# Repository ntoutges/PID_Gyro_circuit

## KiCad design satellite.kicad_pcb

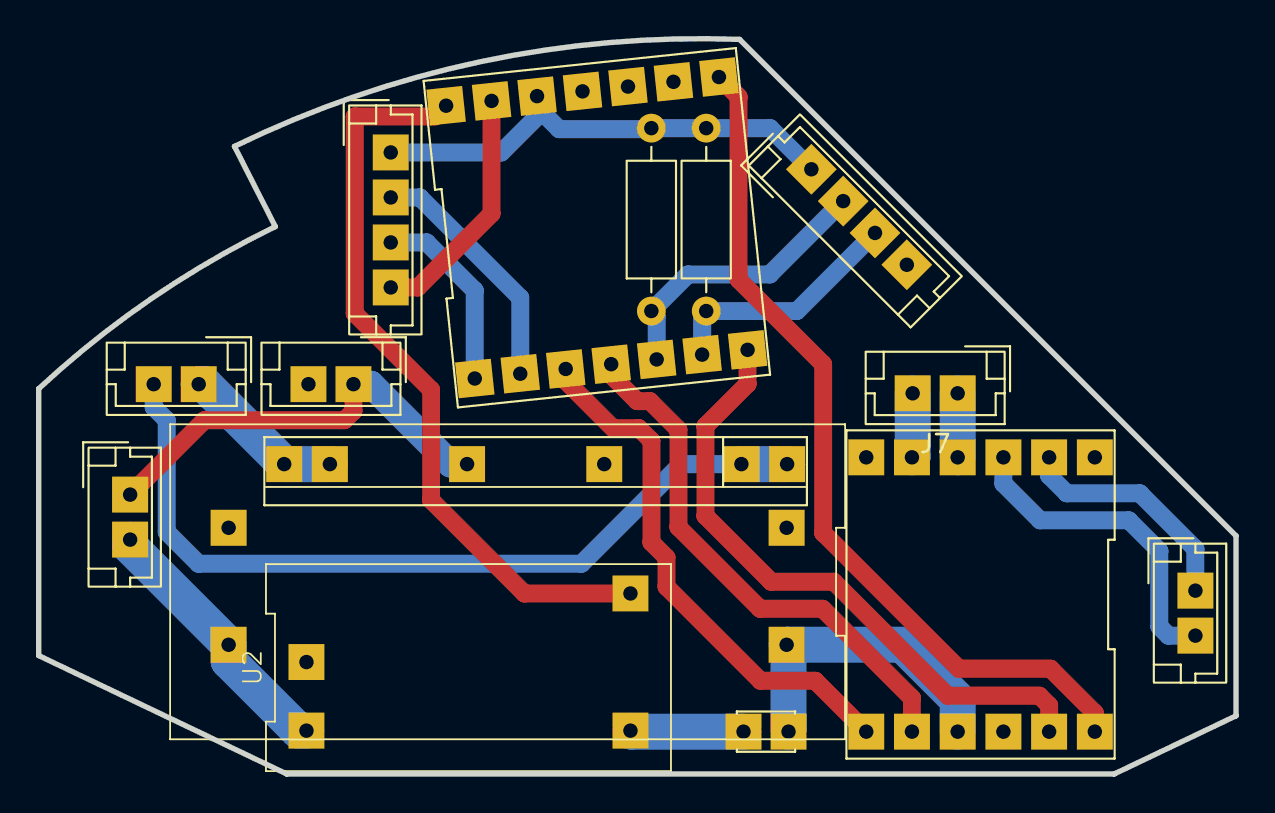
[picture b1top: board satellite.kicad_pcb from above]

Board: 2 copper layers, 66.5 x 40.8 mm, 15 parts (0 on the bottom side), 20 nets.

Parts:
C1: 10uF; C_Disc_D3.0mm_W2.0mm_P2.50mm
J1: BATT; JST_EH_B2B-EH-A_1x02_P2.50mm_Vertical
J2: PWR; JST_EH_B2B-EH-A_1x02_P2.50mm_Vertical
J3: I2C; JST_EH_B4B-EH-A_1x04_P2.50mm_Vertical
J4: MOTOR1; JST_EH_B2B-EH-A_1x02_P2.50mm_Vertical
J5: GPIO; JST_EH_B4B-EH-A_1x04_P2.50mm_Vertical
J6: PWR_SW; JST_EH_B2B-EH-A_1x02_P2.50mm_Vertical
J7: MOTOR2; JST_EH_B2B-EH-A_1x02_P2.50mm_Vertical
R1, R2: 3.7k; R_Axial_DIN0207_L6.3mm_D2.5mm_P10.16mm_Horizontal
U1: xiao
U2: 3V7_boost
U3: 18650_BMS
U4: MT3608
U6: DRV8833

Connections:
+3.3V: J3.1, J5.1, R1.1, R2.2, U1.12 (+3V3)
+5V: U1.14 (+5V), U2.4 (Vout+)
+10V: C1.1, U4.1 (Vout+), U6.9 (Vcc)
/Vin: J2.1, J6.1, U3.3 (Pwr+)
GND: C1.2, J2.2, J3.4, J5.4, U1.13 (GND), U2.1 (Vin-), U2.3 (Vout-), U3.2 (Pwr-), U4.2 (Vout-), U4.3 (Vin-), U6.10 (GND)
GPIO0: J5.3, U1.1 (0)
GPIO1: J5.2, U1.2 (1)
M_A: U1.3 (2), U6.7 (in1)
M_Aout: J4.1, U6.2 (out1)
M_B: U1.4 (3), U6.8 (in2)
M_Bout: J4.2, U6.3 (out2)
M_C: U1.7 (6), U6.11 (in3)
M_Cout: J7.1, U6.4 (out3)
M_D: U1.8 (7), U6.12 (in4)
M_Dout: J7.2, U6.5 (out4)
unnamed: J1.1, U3.4 (Batt+)
unnamed: J1.2, U3.1 (Batt-)
unnamed: J6.2, U2.2 (Vin+), U4.4 (Vin+)
SCL: J3.3, R1.2, U1.6 (5)
SDA: J3.2, R2.1, U1.5 (4)
